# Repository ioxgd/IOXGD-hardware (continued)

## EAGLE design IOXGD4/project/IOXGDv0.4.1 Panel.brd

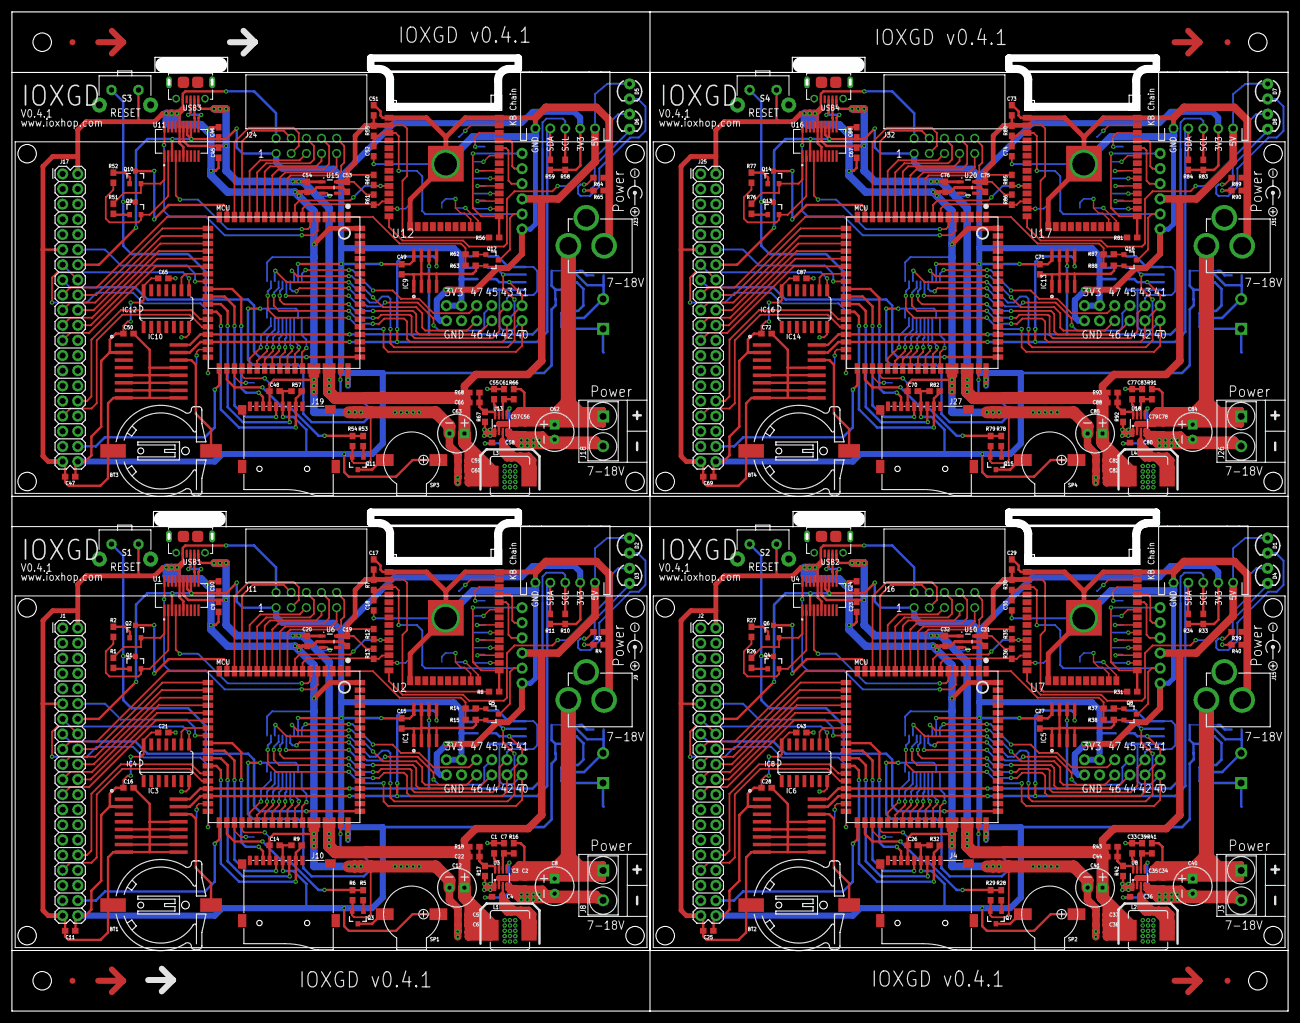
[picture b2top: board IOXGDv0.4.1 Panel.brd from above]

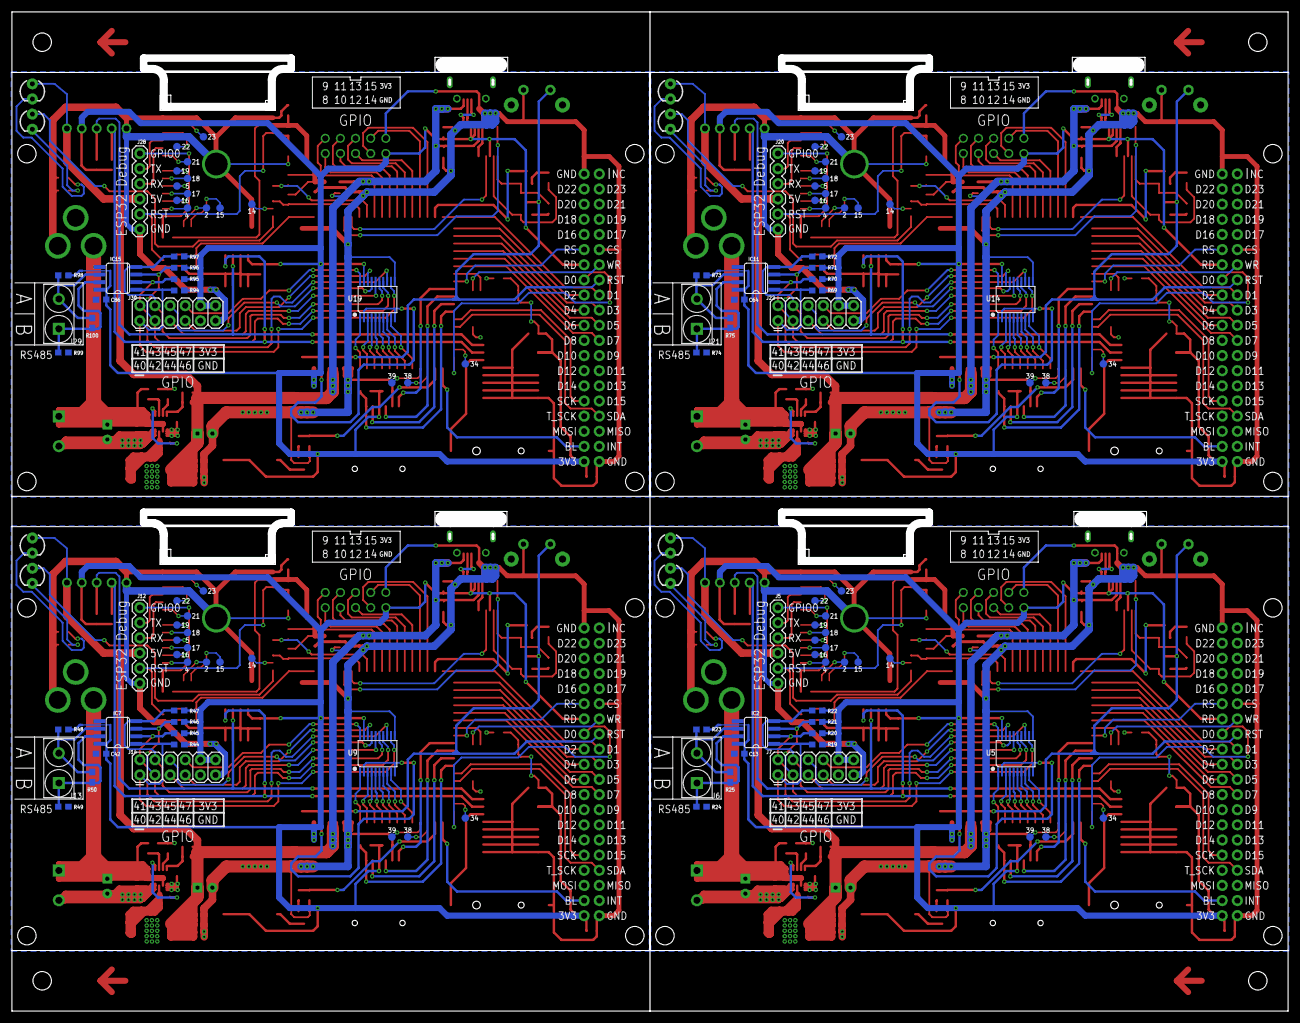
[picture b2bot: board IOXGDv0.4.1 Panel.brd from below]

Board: 2 copper layers, 211.6 x 165.1 mm, 372 parts (112 on the bottom side), 388 nets.

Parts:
BT1, BT2, BT3, BT4: CH291-1220LF
C1, C3, C4, C7, C9, C10, C11, C13, C14, C15, C16, C17, C18, C19, C20, C21, C23, C24, C25, C26, C27, C28, C29, C30, C31, C32, C33, C35, C36, C39, C42, C43, C45, C46, C47, C48, C49, C50, C51, C52, C53, C54, C55, C57, C58, C61, C64, C65, C67, C68, C69, C70, C71, C72, C73, C74, C75, C76, C77, C79, C80, C83, C86, C87: 0.1uF; 0603
C2, C34, C56, C78: 22uF; 0805
C5, C6, C37, C38, C59, C60, C81, C82: 22uF; 0603
C8, C40, C62, C84: 100uF; CPOL-RADIAL-2.5MM-6.5MM
C12, C41, C63, C85: 330uF; CPOL-RADIAL-2.5MM-6.5MM
C22, C44, C66, C88: 13pF; 0603
D1, D2, D3, D4, D5, D6, D7, D8: LED_3MM
E$1, E$2, E$3, E$4: FIDUCIAL-1X2
IC1, IC5, IC9, IC13: BR24G32F; SO-08
IC2, IC7, IC11, IC15: MAX481CSA; SO08
IC3, IC6, IC10, IC14: DS3231/SO; SO16W
IC4, IC8, IC12, IC16: 74HC04D; SO14
J1, J2, J17, J25: LCD; 2X20
J3, J8, J18, J26: GREEN-2P-5.0; H2-5.0-10.5X8.0MM
J4, J10, J19, J27: MICROSD-9P; MICRO-SD9+4P-SMD-16.1X14.5X1.85MM
J5, J12, J20, J28: 1X06
J6, J13, J21, J29: RS485; H2-5.0-10.5X8.0MM
J7, J14, J22, J30: 2X6 FEMALE; 2X6
J9, J15, J23, J31: POWER_JACK; POWER_JACK_PTH
J11, J16, J24, J32: 612010235221
L1, L2, L3, L4: 6R8; MCS0630SERIES
MCU1, MCU2, MCU3, MCU4: SIPEED_M1; M1
Q1, Q2, Q3, Q4, Q5, Q6, Q7, Q8, Q9, Q10, Q11, Q12, Q13, Q14, Q15, Q16: SI2302; SOT23-3
R1, R2, R7, R8, R9, R10, R11, R12, R13, R19, R20, R21, R22, R26, R27, R30, R31, R32, R33, R34, R35, R36, R44, R45, R46, R47, R51, R52, R55, R56, R57, R58, R59, R60, R61, R69, R70, R71, R72, R76, R77, R80, R81, R82, R83, R84, R85, R86, R94, R95, R96, R97: 10k; 0603
R3, R4, R39, R40, R64, R65, R89, R90: 220; 0603
R5, R14, R28, R37, R53, R62, R78, R87: 20; 0603
R6, R15, R16, R18, R29, R38, R41, R43, R54, R63, R66, R68, R79, R88, R91, R93: 100k; 0603
R17, R42, R67, R92: 13.9k; 0603
R23, R24, R48, R49, R73, R74, R98, R99: 20k; 0603
R25, R50, R75, R100: 120; 0603
S1, S2, S3, S4: RESET; TC-020X
SP1, SP2, SP3, SP4: SMD-BUZZER1
TP1, TP2, TP3, TP4, TP5, TP6, TP7, TP8, TP9, TP10, TP11, TP12, TP13, TP14, TP15, TP16, TP17, TP18, TP19, TP20, TP21, TP22, TP23, TP24, TP25, TP26, TP27, TP28, TP29, TP30, TP31, TP32, TP33, TP34, TP35, TP36, TP37, TP38, TP39, TP40, TP41, TP42, TP43, TP44, TP45, TP46, TP47, TP48, TP49, TP50, TP51, TP52, TP53, TP54, TP55, TP56, TP57, TP58, TP59, TP60: TEST-POINT3X5; PAD.03X.05
U1, U4, U11, U16: FT231XS-R; SOP63P599X175-20N
U2, U7, U12, U17: ESP-WROOM-32
U3, U8, U13, U18: MP2225GJ-Z; TSOT-23-8
U5, U9, U14, U19: TXS0108E; TSSOP20-0.65-6.5X4.4MM
U6, U10, U15, U20: 3.3V; SOT23-5
U$1, U$2, U$3, U$4: KB_CHAIN-H; JST5PIN
USB1, USB2, USB3, USB4: ZX62-B-5PA; MICRO-USB5+6P-SMD-0.65-AB

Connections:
1.8V: MCU1.53, U5.2, U5.10
1.8V1: MCU2.53, U9.2, U9.10
1.8V2: MCU3.53, U14.2, U14.10
1.8V3: MCU4.53, U19.2, U19.10
+3V1: C24.1, C25.1, C26.1, C27.1, C28.1, C42.1, C43.1, IC5.8, IC6.2, IC7.8, IC8.14, J2.14, J2.40, J4.4, J14.10, J14.12, J16.1, MCU2.54, R32.2, R33.2, R34.2, R44.2, R45.2, R46.2, R47.2, R48.2, SP2.+, U4.3, U4.13, U4.14, U9.19, U$1.4
+3V2: C46.1, C47.1, C48.1, C49.1, C50.1, C64.1, C65.1, IC9.8, IC10.2, IC11.8, IC12.14, J17.14, J17.40, J19.4, J22.10, J22.12, J24.1, MCU3.54, R57.2, R58.2, R59.2, R69.2, R70.2, R71.2, R72.2, R73.2, SP3.+, U11.3, U11.13, U11.14, U14.19, U$3.4
+3V3: C10.1, C11.1, C13.1, C14.1, C15.1, C16.1, C21.1, IC1.8, IC2.8, IC3.2, IC4.14, J1.14, J1.40, J7.10, J7.12, J10.4, J11.1, MCU1.54, R9.2, R10.2, R11.2, R19.2, R20.2, R21.2, R22.2, R23.2, SP1.+, U1.3, U1.13, U1.14, U5.19, U$2.4
+3V4: C68.1, C69.1, C70.1, C71.1, C72.1, C86.1, C87.1, IC13.8, IC14.2, IC15.8, IC16.14, J25.14, J25.40, J27.4, J30.10, J30.12, J32.1, MCU4.54, R82.2, R83.2, R84.2, R94.2, R95.2, R96.2, R97.2, R98.2, SP4.+, U16.3, U16.13, U16.14, U19.19, U$4.4
+5V: C5.1, C6.1, C9.1, C12.1, C20.1, C22.2, D2.A, J5.4, L1.P$2, MCU1.51, MCU1.52, R18.2, U1.15, U6.1, U6.3, U$2.5, USB1.1
+5V1: C23.1, C32.1, C37.1, C38.1, C41.1, C44.2, D1.A, J12.4, L2.P$2, MCU2.51, MCU2.52, R43.2, U4.15, U10.1, U10.3, U$1.5, USB2.1
+5V2: C45.1, C54.1, C59.1, C60.1, C63.1, C66.2, D5.A, J20.4, L3.P$2, MCU3.51, MCU3.52, R68.2, U11.15, U15.1, U15.3, U$3.5, USB3.1
+5V3: C67.1, C76.1, C81.1, C82.1, C85.1, C88.2, D7.A, J28.4, L4.P$2, MCU4.51, MCU4.52, R93.2, U16.15, U20.1, U20.3, U$4.5, USB4.1
A: IC2.6, J6.2, R23.1, R25.1
A1: IC7.6, J13.2, R48.1, R50.1
A2: IC11.6, J21.2, R73.1, R75.1
A3: IC15.6, J29.2, R98.1, R100.1
B: IC2.7, J6.1, R24.2, R25.2
B1: IC7.7, J13.1, R49.2, R50.2
B2: IC11.7, J21.1, R74.2, R75.2
B3: IC15.7, J29.1, R99.2, R100.2
BOOT: MCU1.17, Q2.3
BOOT1: MCU2.17, Q6.3
BOOT2: MCU3.17, Q10.3
BOOT3: MCU4.17, Q14.3
BUZZER: MCU1.38, R5.1, R6.2
BUZZER1: MCU2.38, R28.1, R29.2
BUZZER2: MCU3.38, R53.1, R54.2
BUZZER3: MCU4.38, R78.1, R79.2
DTR#: Q2.2, R1.1, U1.1
DTR#1: Q6.2, R26.1, U4.1
DTR#2: Q10.2, R51.1, U11.1
DTR#3: Q14.2, R76.1, U16.1
ESP32_GPIO0: J5.1, R8.1, U2.25
ESP32_GPIO1: J12.1, R31.1, U7.25
ESP32_GPIO2: TP10.P$1, U2.24
ESP32_GPIO3: D4.A, U7.14
ESP32_GPIO4: TP9.P$1, U2.26
ESP32_GPIO5: TP6.P$1, U2.29
ESP32_GPIO6: TP12.P$1, U7.37
ESP32_GPIO7: TP15.P$1, U7.36
ESP32_GPIO8: TP19.P$1, U7.31
ESP32_GPIO9: TP18.P$1, U7.33
ESP32_GPIO10: TP20.P$1, U7.30
ESP32_GPIO11: TP21.P$1, U7.29
ESP32_GPIO12: D3.A, U2.14
ESP32_GPIO13: TP22.P$1, U7.28
ESP32_GPIO14: TP13.P$1, U2.13
ESP32_GPIO15: TP11.P$1, U2.23
ESP32_GPIO16: TP8.P$1, U2.27
ESP32_GPIO17: TP7.P$1, U2.28
ESP32_GPIO18: TP5.P$1, U2.30
ESP32_GPIO19: TP4.P$1, U2.31
ESP32_GPIO20: TP23.P$1, U7.27
ESP32_GPIO21: TP3.P$1, U2.33
ESP32_GPIO22: TP2.P$1, U2.36
ESP32_GPIO23: TP1.P$1, U2.37
ESP32_GPIO24: TP24.P$1, U7.26
ESP32_GPIO25: TP25.P$1, U7.24
ESP32_GPIO26: TP26.P$1, U7.23
ESP32_GPIO27: TP27.P$1, U7.13
ESP32_GPIO28: J20.1, R56.1, U12.25
ESP32_GPIO29: D6.A, U12.14
ESP32_GPIO30: TP31.P$1, U12.37
ESP32_GPIO31: TP32.P$1, U12.36
ESP32_GPIO32: TP34.P$1, U12.31
ESP32_GPIO33: TP33.P$1, U12.33
ESP32_GPIO34: TP35.P$1, U12.30
ESP32_GPIO35: TP36.P$1, U12.29
ESP32_GPIO36: TP37.P$1, U12.28
ESP32_GPIO37: TP38.P$1, U12.27
ESP32_GPIO38: TP39.P$1, U12.26
ESP32_GPIO39: TP40.P$1, U12.24
ESP32_GPIO40: TP41.P$1, U12.23
ESP32_GPIO41: TP42.P$1, U12.13
ESP32_GPIO42: J28.1, R81.1, U17.25
ESP32_GPIO43: D8.A, U17.14
ESP32_GPIO44: TP46.P$1, U17.37
ESP32_GPIO45: TP47.P$1, U17.36
ESP32_GPIO46: TP49.P$1, U17.31
ESP32_GPIO47: TP48.P$1, U17.33
ESP32_GPIO48: TP50.P$1, U17.30
ESP32_GPIO49: TP51.P$1, U17.29
ESP32_GPIO50: TP52.P$1, U17.28
ESP32_GPIO51: TP53.P$1, U17.27
ESP32_GPIO52: TP54.P$1, U17.26
ESP32_GPIO53: TP55.P$1, U17.24
ESP32_GPIO54: TP56.P$1, U17.23
ESP32_GPIO55: TP57.P$1, U17.13
ESP32_RESET: MCU1.1, R14.1, R15.2
ESP32_RESET1: MCU2.1, R37.1, R38.2
ESP32_RESET2: MCU3.1, R62.1, R63.2
ESP32_RESET3: MCU4.1, R87.1, R88.2
ESP32_RST: C18.1, J5.5, Q5.3, R7.1, U2.3
ESP32_RST1: C30.1, J12.5, Q8.3, R30.1, U7.3
ESP32_RST2: C52.1, J20.5, Q12.3, R55.1, U12.3
ESP32_RST3: C74.1, J28.5, Q16.3, R80.1, U17.3
ESP32_RX: J5.3, U2.34
ESP32_RX1: J12.3, U7.34
ESP32_RX2: J20.3, U12.34
ESP32_RX3: J28.3, U17.34
ESP32_TX: J5.2, U2.35
ESP32_TX1: J12.2, U7.35
ESP32_TX2: J20.2, U12.35
ESP32_TX3: J28.2, U17.35
GND: BT1.-, C1.2, C2.2, C3.2, C5.2, C6.2, C7.2, C8.2, C9.2, C10.2, C11.2, C12.2, C13.2, C14.2, C15.2, C16.2, C17.2, C18.2, C19.2, C20.2, C21.2, IC1.1, IC1.2, IC1.3, IC1.4, IC1.7, IC2.5, IC3.5, IC3.6, IC3.7, IC3.8, IC3.9, IC3.10, IC3.11, IC3.12, IC3.13, IC4.7, J1.2, J1.11, J1.39, J5.6, J7.9, J7.11, J8.2, J9.GND, J10.6, J11.2, MCU1.49, MCU1.50, MCU1.72, Q3.2, Q5.2, R3.1, R4.1, R6.1, R15.1, R17.1, R24.1, S1.2, U1.6, U1.16, U2.1, U2.15, U2.38, U2.GND, U3.1, U3.4, U5.11, U6.2, U$2.1, USB1.5
GND1: BT2.-, C23.2, C24.2, C25.2, C26.2, C27.2, C28.2, C29.2, C30.2, C31.2, C32.2, C33.2, C34.2, C35.2, C37.2, C38.2, C39.2, C40.2, C41.2, C42.2, C43.2, IC5.1, IC5.2, IC5.3, IC5.4, IC5.7, IC6.5, IC6.6, IC6.7, IC6.8, IC6.9, IC6.10, IC6.11, IC6.12, IC6.13, IC7.5, IC8.7, J2.2, J2.11, J2.39, J3.2, J4.6, J12.6, J14.9, J14.11, J15.GND, J16.2, MCU2.49, MCU2.50, MCU2.72, Q7.2, Q8.2, R29.1, R38.1, R39.1, R40.1, R42.1, R49.1, S2.2, U4.6, U4.16, U7.1, U7.15, U7.38, U7.GND, U8.1, U8.4, U9.11, U10.2, U$1.1, USB2.5
GND2: BT3.-, C45.2, C46.2, C47.2, C48.2, C49.2, C50.2, C51.2, C52.2, C53.2, C54.2, C55.2, C56.2, C57.2, C59.2, C60.2, C61.2, C62.2, C63.2, C64.2, C65.2, IC9.1, IC9.2, IC9.3, IC9.4, IC9.7, IC10.5, IC10.6, IC10.7, IC10.8, IC10.9, IC10.10, IC10.11, IC10.12, IC10.13, IC11.5, IC12.7, J17.2, J17.11, J17.39, J18.2, J19.6, J20.6, J22.9, J22.11, J23.GND, J24.2, MCU3.49, MCU3.50, MCU3.72, Q11.2, Q12.2, R54.1, R63.1, R64.1, R65.1, R67.1, R74.1, S3.2, U11.6, U11.16, U12.1, U12.15, U12.38, U12.GND, U13.1, U13.4, U14.11, U15.2, U$3.1, USB3.5
GND3: BT4.-, C67.2, C68.2, C69.2, C70.2, C71.2, C72.2, C73.2, C74.2, C75.2, C76.2, C77.2, C78.2, C79.2, C81.2, C82.2, C83.2, C84.2, C85.2, C86.2, C87.2, IC13.1, IC13.2, IC13.3, IC13.4, IC13.7, IC14.5, IC14.6, IC14.7, IC14.8, IC14.9, IC14.10, IC14.11, IC14.12, IC14.13, IC15.5, IC16.7, J25.2, J25.11, J25.39, J26.2, J27.6, J28.6, J30.9, J30.11, J31.GND, J32.2, MCU4.49, MCU4.50, MCU4.72, Q15.2, Q16.2, R79.1, R88.1, R89.1, R90.1, R92.1, R99.1, S4.2, U16.6, U16.16, U17.1, U17.15, U17.38, U17.GND, U18.1, U18.4, U19.11, U20.2, U$4.1, USB4.5
I2C0_SCL: J1.32, MCU1.31
I2C0_SCL1: J2.32, MCU2.31
I2C0_SCL2: J17.32, MCU3.31
I2C0_SCL3: J25.32, MCU4.31
I2C0_SDA: J1.33, MCU1.32
I2C0_SDA1: J2.33, MCU2.32
I2C0_SDA2: J17.33, MCU3.32
I2C0_SDA3: J25.33, MCU4.32
I2C1_SCL: IC1.6, IC3.16, MCU1.33, R10.1, U$2.3
I2C1_SCL1: IC5.6, IC6.16, MCU2.33, R33.1, U$1.3
I2C1_SCL2: IC9.6, IC10.16, MCU3.33, R58.1, U$3.3
I2C1_SCL3: IC13.6, IC14.16, MCU4.33, R83.1, U$4.3
I2C1_SDA: IC1.5, IC3.15, MCU1.34, R11.1, U$2.2
I2C1_SDA1: IC5.5, IC6.15, MCU2.34, R34.1, U$1.2
I2C1_SDA2: IC9.5, IC10.15, MCU3.34, R59.1, U$3.2
I2C1_SDA3: IC13.5, IC14.15, MCU4.34, R84.1, U$4.2
IO1: J16.10, MCU2.9
IO2: J16.9, MCU2.10
IO3: J16.8, MCU2.11
IO4: J16.7, MCU2.12
IO5: J16.6, MCU2.13
IO6: J16.5, MCU2.14
IO7: J16.4, MCU2.15
IO8: J11.10, MCU1.9
IO9: J11.9, MCU1.10
IO10: J11.8, MCU1.11
IO11: J11.7, MCU1.12
IO12: J11.6, MCU1.13
IO13: J11.5, MCU1.14
IO14: J11.4, MCU1.15
IO15: J11.3, MCU1.16
IO16: J16.3, MCU2.16
IO17: IC7.1, J14.1, R44.1, U9.12
IO18: IC7.2, J14.2, R45.1, U9.13
IO19: IC7.3, J14.3, R46.1, U9.14
IO20: IC7.4, J14.4, R47.1, U9.15
IO21: J14.5, U9.16
IO22: J14.6, U9.17
IO23: J14.7, U9.18
IO24: IC4.9, MCU1.25
IO25: J14.8, U9.20
IO26: IC8.9, MCU2.25
IO27: J24.10, MCU3.9
IO28: J24.9, MCU3.10
IO29: J24.8, MCU3.11
IO30: J24.7, MCU3.12
IO31: J24.6, MCU3.13
IO32: J24.5, MCU3.14
IO33: J24.4, MCU3.15
IO34: J24.3, MCU3.16
IO35: IC11.1, J22.1, R69.1, U14.12
IO36: IC11.2, J22.2, R70.1, U14.13
IO37: IC11.3, J22.3, R71.1, U14.14
IO38: IC11.4, J22.4, R72.1, U14.15
IO39: J22.5, U14.16
IO40: IC2.1, J7.1, R19.1, U5.12
IO41: IC2.2, J7.2, R20.1, U5.13
IO42: IC2.3, J7.3, R21.1, U5.14
IO43: IC2.4, J7.4, R22.1, U5.15
IO44: J7.5, U5.16
IO45: J7.6, U5.17
IO46: J7.7, U5.18
IO47: J7.8, U5.20
IO48: J22.6, U14.17
IO49: J22.7, U14.18
IO50: J22.8, U14.20
IO51: IC12.9, MCU3.25
IO52: J32.10, MCU4.9
IO53: J32.9, MCU4.10
IO54: J32.8, MCU4.11
IO55: J32.7, MCU4.12
IO56: J32.6, MCU4.13
IO57: J32.5, MCU4.14
IO58: J32.4, MCU4.15
IO59: J32.3, MCU4.16
IO60: IC15.1, J30.1, R94.1, U19.12
IO61: IC15.2, J30.2, R95.1, U19.13
IO62: IC15.3, J30.3, R96.1, U19.14
IO63: IC15.4, J30.4, R97.1, U19.15
IO64: J30.5, U19.16
IO65: J30.6, U19.17
IO66: J30.7, U19.18
IO67: J30.8, U19.20
IO68: IC16.9, MCU4.25
IOA1: MCU2.41, U9.9
IOA2: MCU2.42, U9.8
IOA3: MCU2.43, U9.7
IOA4: MCU2.44, U9.6
IOA5: MCU2.45, U9.5
IOA6: MCU2.46, U9.4
IOA7: MCU2.47, U9.3
IOA8: MCU2.48, U9.1
IOA9: MCU2.39, TP29.P$1
IOA10: MCU2.40, TP30.P$1
IOA11: MCU3.41, U14.9
IOA12: MCU3.42, U14.8
IOA13: MCU3.43, U14.7
IOA14: MCU3.44, U14.6
IOA15: MCU3.45, U14.5
IOA16: MCU3.46, U14.4
IOA17: MCU3.47, U14.3
IOA18: MCU3.48, U14.1
IOA19: MCU3.39, TP44.P$1
IOA20: MCU3.40, TP45.P$1
IOA21: MCU4.41, U19.9
IOA22: MCU4.42, U19.8
IOA23: MCU4.43, U19.7
IOA24: MCU4.44, U19.6
IOA25: MCU4.45, U19.5
IOA26: MCU4.46, U19.4
IOA27: MCU4.47, U19.3
IOA28: MCU4.48, U19.1
IOA29: MCU4.39, TP59.P$1
IOA30: MCU4.40, TP60.P$1
IOA38: MCU1.39, TP16.P$1
IOA39: MCU1.40, TP17.P$1
IOA40: MCU1.41, U5.9
IOA41: MCU1.42, U5.8
IOA42: MCU1.43, U5.7
IOA43: MCU1.44, U5.6
IOA44: MCU1.45, U5.5
IOA45: MCU1.46, U5.4
IOA46: MCU1.47, U5.3
IOA47: MCU1.48, U5.1
ISP_RX: MCU1.5, U1.20
ISP_RX1: MCU2.5, U4.20
ISP_RX2: MCU3.5, U11.20
ISP_RX3: MCU4.5, U16.20
ISP_TX: MCU1.6, U1.4
ISP_TX1: MCU2.6, U4.4
ISP_TX2: MCU3.6, U11.4
ISP_TX3: MCU4.6, U16.4
LCD_BL: J1.38, MCU1.37
LCD_BL1: J2.38, MCU2.37
LCD_BL2: J17.38, MCU3.37
LCD_BL3: J25.38, MCU4.37
LCD_D0: J1.16, MCU1.36
LCD_D1: J1.17, MCU1.18
LCD_D2: J1.18, MCU1.19
LCD_D3: J1.19, MCU1.20
LCD_D4: J1.20, MCU1.21
LCD_D5: J1.21, MCU1.22
LCD_D6: J1.22, MCU1.23
LCD_D7: J1.23, MCU1.24
LCD_D8: J2.17, MCU2.18
LCD_D9: J2.18, MCU2.19
LCD_D10: J2.19, MCU2.20
LCD_D11: J2.20, MCU2.21
LCD_D12: J2.21, MCU2.22
LCD_D13: J2.22, MCU2.23
LCD_D14: J2.23, MCU2.24
LCD_D15: J2.16, MCU2.36
LCD_D16: J17.17, MCU3.18
LCD_D17: J17.18, MCU3.19
LCD_D18: J17.19, MCU3.20
LCD_D19: J17.20, MCU3.21
LCD_D20: J17.21, MCU3.22
LCD_D21: J17.22, MCU3.23
LCD_D22: J17.23, MCU3.24
LCD_D23: J17.16, MCU3.36
LCD_D24: J25.17, MCU4.18
LCD_D25: J25.18, MCU4.19
LCD_D26: J25.19, MCU4.20
LCD_D27: J25.20, MCU4.21
LCD_D28: J25.21, MCU4.22
LCD_D29: J25.22, MCU4.23
LCD_D30: J25.23, MCU4.24
LCD_D31: J25.16, MCU4.36
LCD_RS: J1.12, MCU1.26
LCD_RS1: J2.12, MCU2.26
LCD_RS2: J17.12, MCU3.26
LCD_RS3: J25.12, MCU4.26
LCD_WR: IC4.8, J1.13
LCD_WR1: IC8.8, J2.13
LCD_WR2: IC12.8, J17.13
LCD_WR3: IC16.8, J25.13
unnamed: U1.11, USB1.3
unnamed: U1.12, USB1.2
unnamed: Q2.1, R2.2
unnamed: Q1.1, R1.2
unnamed: BT1.+, IC3.14
unnamed: C1.1, U3.7
unnamed: D2.K, R3.2
unnamed: D3.K, R4.2
unnamed: U4.11, USB2.3
unnamed: Q3.3, SP1.-
unnamed: Q3.1, R5.2
unnamed: C4.1, U3.5
unnamed: C4.2, L1.P$1, U3.3
unnamed: C22.1, R17.2, R18.1, U3.8
unnamed: Q5.1, R14.2
unnamed: U4.12, USB2.2
unnamed: Q6.1, R27.2
unnamed: Q4.1, R26.2
unnamed: Q7.3, SP2.-
unnamed: Q7.1, R28.2
unnamed: Q8.1, R37.2
unnamed: BT2.+, IC6.14
unnamed: D1.K, R39.2
unnamed: D4.K, R40.2
unnamed: C33.1, U8.7
unnamed: C36.1, U8.5
unnamed: C36.2, L2.P$1, U8.3
unnamed: C44.1, R42.2, R43.1, U8.8
unnamed: U11.11, USB3.3
unnamed: U11.12, USB3.2
unnamed: Q10.1, R52.2
unnamed: Q9.1, R51.2
unnamed: Q11.3, SP3.-
unnamed: Q11.1, R53.2
unnamed: Q12.1, R62.2
unnamed: BT3.+, IC10.14
unnamed: D5.K, R64.2
unnamed: D6.K, R65.2
unnamed: C55.1, U13.7
unnamed: C58.1, U13.5
unnamed: C58.2, L3.P$1, U13.3
unnamed: C66.1, R67.2, R68.1, U13.8
unnamed: U16.11, USB4.3
unnamed: U16.12, USB4.2
unnamed: Q14.1, R77.2
unnamed: Q13.1, R76.2
unnamed: Q15.3, SP4.-
unnamed: Q15.1, R78.2
unnamed: Q16.1, R87.2
unnamed: BT4.+, IC14.14
unnamed: D7.K, R89.2
unnamed: D8.K, R90.2
unnamed: C77.1, U18.7
unnamed: C80.1, U18.5
unnamed: C80.2, L4.P$1, U18.3
unnamed: C88.1, R92.2, R93.1, U18.8
PW-EN: C7.1, R16.1, U3.6
PW-EN1: C39.1, R41.1, U8.6
PW-EN2: C61.1, R66.1, U13.6
PW-EN3: C83.1, R91.1, U18.6
RST: J1.15, MCU1.55, Q1.3, S1.1
RST1: J2.15, MCU2.55, Q4.3, S2.1
RST2: J17.15, MCU3.55, Q9.3, S3.1
RST3: J25.15, MCU4.55, Q13.3, S4.1
RTS#: Q1.2, R2.1, U1.2
RTS#1: Q4.2, R27.1, U4.2
RTS#2: Q9.2, R52.1, U11.2
RTS#3: Q13.2, R77.1, U16.2
SPI0_MISO: J10.7, MCU1.27
SPI0_MISO1: J4.7, MCU2.27
SPI0_MISO2: J19.7, MCU3.27
SPI0_MISO3: J27.7, MCU4.27
SPI0_MOSI: J10.3, MCU1.29
SPI0_MOSI1: J4.3, MCU2.29
SPI0_MOSI2: J19.3, MCU3.29
SPI0_MOSI3: J27.3, MCU4.29
SPI0_SCK: J10.5, MCU1.28
SPI0_SCK1: J4.5, MCU2.28
SPI0_SCK2: J19.5, MCU3.28
SPI0_SCK3: J27.5, MCU4.28
SPI0_SS0: J10.2, MCU1.30, R9.1
SPI0_SS1: MCU1.35, TP14.P$1
SPI0_SS2: MCU2.35, TP28.P$1
SPI0_SS3: J4.2, MCU2.30, R32.1
SPI0_SS4: MCU3.35, TP43.P$1
SPI0_SS5: J19.2, MCU3.30, R57.1
SPI0_SS6: MCU4.35, TP58.P$1
SPI0_SS7: J27.2, MCU4.30, R82.1
VIN: C2.1, C3.1, C8.1, J8.1, J9.PWR, R16.2, U3.2
VIN1: C34.1, C35.1, C40.1, J3.1, J15.PWR, R41.2, U8.2
VIN2: C56.1, C57.1, C62.1, J18.1, J23.PWR, R66.2, U13.2
VIN3: C78.1, C79.1, C84.1, J26.1, J31.PWR, R91.2, U18.2
V_ESP1: C29.1, C31.1, R30.2, R31.2, R35.2, R36.2, U7.2, U10.5
V_ESP2: C51.1, C53.1, R55.2, R56.2, R60.2, R61.2, U12.2, U15.5
V_ESP3: C73.1, C75.1, R80.2, R81.2, R85.2, R86.2, U17.2, U20.5
V_ESP32: C17.1, C19.1, R7.2, R8.2, R12.2, R13.2, U2.2, U6.5
WIFI_RX_MCU_TX: MCU1.8, R12.1, U2.10
WIFI_RX_MCU_TX1: MCU2.8, R35.1, U7.10
WIFI_RX_MCU_TX2: MCU3.8, R60.1, U12.10
WIFI_RX_MCU_TX3: MCU4.8, R85.1, U17.10
WIFI_TX_MCU_RX: MCU1.7, R13.1, U2.12
WIFI_TX_MCU_RX1: MCU2.7, R36.1, U7.12
WIFI_TX_MCU_RX2: MCU3.7, R61.1, U12.12
WIFI_TX_MCU_RX3: MCU4.7, R86.1, U17.12

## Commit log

2019-11-18 เพิ่มข้อมูลบอร์ด IOXGD4 v0.4.1
